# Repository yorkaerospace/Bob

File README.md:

# ARCHIVED REPO
Keeping hardware and software in the same repository causes headache on top of headache. To that end, this repo was archived on 2023-07-08 and further development will continue in the following repos:
- [ProtonNumber/Bob-Firmware](https://github.com/ProtonNumber/Bob-Firmware)  
- [ProtonNumber/Bob-Hardware](https://github.com/ProtonNumber/Bob-Hardware)
- [ProtonNumber/Bob-Drivers](https://github.com/ProtonNumber/Bob-Drivers)

# Bob

Simple RP2040 based datalogger.

## Rev 3 Specs:

 - 8MB of flash storage (Winbond W25Q64)
 - Barometer/Altimiter (HopeRF HP203B)
 - 6-Axis IMU (QST QMI8658C)
 - 3-Axis Magnetometer (QST QMC5883L)
 
 See docs folder for datasheets.

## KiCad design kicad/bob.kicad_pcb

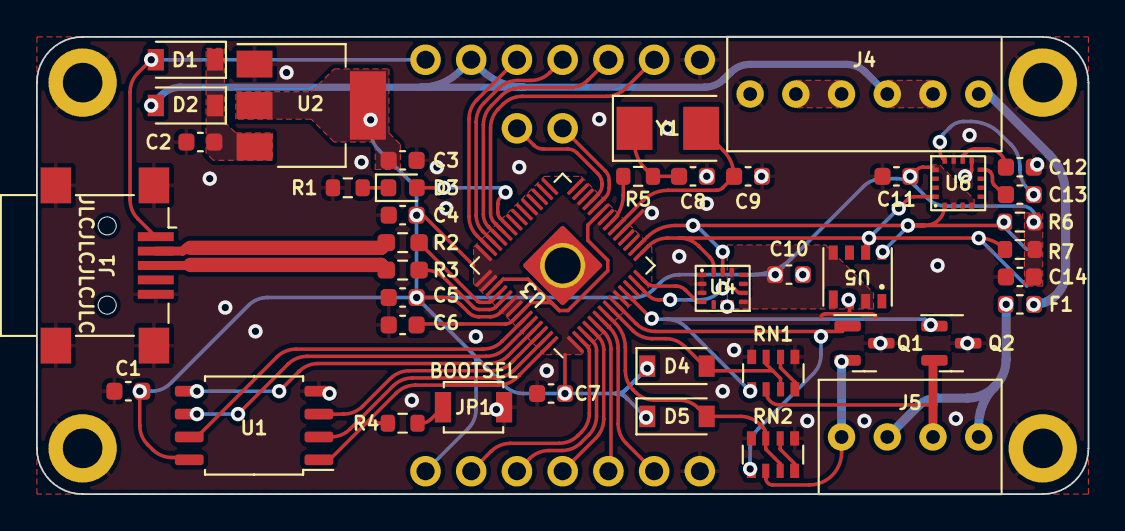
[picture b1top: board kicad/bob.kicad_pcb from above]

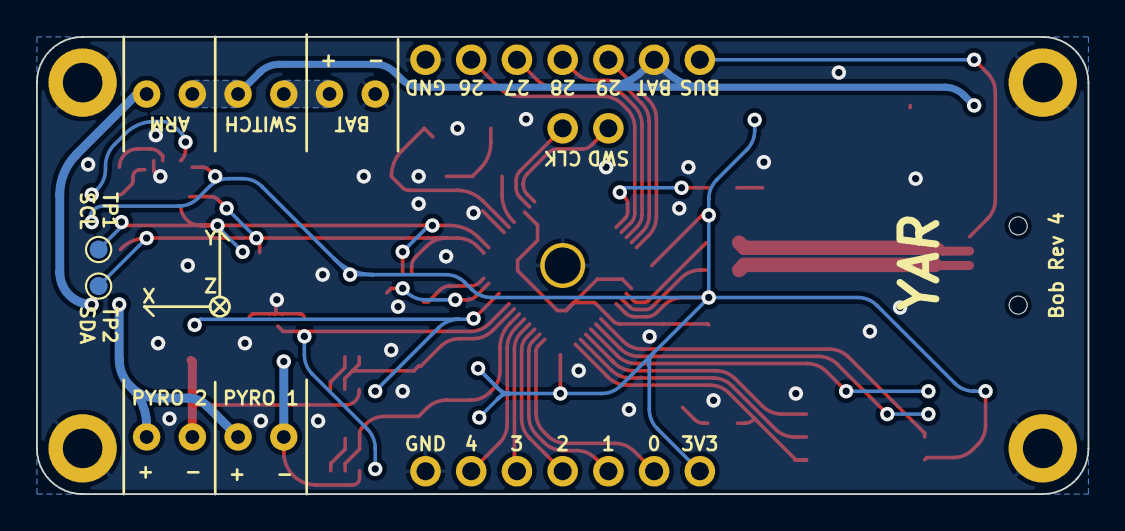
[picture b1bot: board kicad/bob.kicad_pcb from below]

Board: 2 copper layers, 58.4 x 25.4 mm, 52 parts (4 on the bottom side), 51 nets.

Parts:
C1, C5, C7, C10, C11, C14: 100n; C_0603_1608Metric
C2, C3: 10u; C_0603_1608Metric
C4, C6: 1u; C_0603_1608Metric
C8, C9: 4p; C_0603_1608Metric
C12: 4.7u; C_0603_1608Metric
C13: 220n; C_0603_1608Metric
D1, D2, D4, D5: 1N4007; D_SOD-123
D3: RED; LED_0603_1608Metric
F1: Polyfuse; Fuse_0603_1608Metric
H1, H2, H3, H4: MountingHole_Pad; MountingHole_2.2mm_M2_DIN965_Pad
J1: Mini USB Female; USB_Mini-B_Lumberg_2486_01_Horizontal
J2, J3: GPIO (Optional); PinHeader_1x07_P2.54mm_Vertical_NoSilk
J4: Screw Terminal, 2.54mm; ScrewTerm_2.54x06
J5: Conn_01x04_Male; ScrewTerm_2.54x04
J6: Conn_01x03_Male; PinHeader_1x02_P2.54mm_Vertical
JP1: BOOTSEL; SW_SPST_B3U-1000P
Q1, Q2: IRFML8244TRPBF; SOT-23
R1: 220; R_0603_1608Metric
R2, R3: 27; R_0603_1608Metric_Pad0.98x0.95mm_HandSolder
R4, R5: 1k; R_0603_1608Metric
R6, R7: 10k; R_0603_1608Metric
RN1, RN2: 22k; R_Array_Convex_4x0603
TP1, TP2: TestPoint; TestPoint_Pad_D1.0mm
U1: W25Q64JVSS; SOIC-8_5.23x5.23mm_P1.27mm
U2: AMS1117-3.3; SOT-223-3_TabPin2
U3: RP2040; RP2040-QFN-56_HS
U4: QMI8658C; QMI8658C-LGA14
U5: HP203B; HP203B-LGA8
U6: QMC5883L; QMC5883L-LGA16
Y1: 12MHz; Crystal_SMD_5032-2Pin_5.0x3.2mm
YAR: LOGO; YAR_Logo

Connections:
+1V1: C6.1, U3.23 (DVDD), U3.45 (VREG_VOUT), U3.50 (DVDD)
+3V3: C1.1, C3.1, C4.1, C5.1, C7.1, C10.1, C11.1, C14.1, D4.1 (K), D5.1 (K), J3.1, R6.2, R7.2, U1.8 (VCC), U2.2 (VO), U3.1 (IOVDD), U3.10 (IOVDD), U3.22 (IOVDD), U3.26 (RUN), U3.33 (IOVDD), U3.42 (IOVDD), U3.43 (ADC_AVDD), U3.44 (VREG_IN), U3.48 (USB_VDD), U3.49 (IOVDD), U4.8 (VDD), U4.12 (CS), U5.3 (VDD), U5.8 (CSB), U6.2 (VDD), U6.4 (S1), U6.13 (VIO)
+BATT: D2.2 (A), J2.2, J4.4, J4.5
ARM: F1.2, J5.2, J5.4
Cont 1: D5.2 (A), RN2.3 (R3.1), RN2.7 (R2.2), U3.7 (GPIO5)
Cont 2: D4.2 (A), RN1.3 (R3.1), RN1.7 (R2.2), U3.8 (GPIO6)
Fire 1: J5.1, Q1.2 (D), RN2.2 (R2.1)
Fire 2: J5.3, Q2.2 (D), RN1.2 (R2.1)
GND: C1.2, C2.2, C3.2, C4.2, C5.2, C6.2, C7.2, C8.1, C9.1, C10.2, C11.2, C12.1, C14.2, H1.1, H2.1, H3.1, H4.1, J1.5 (GND), J1.6 (Shield), J2.7, J3.7, J4.1, JP1.1 (A), Q1.3 (S), Q2.3 (S), R1.2, RN1.5 (R4.2), RN1.8 (R1.2), RN2.5 (R4.2), RN2.8 (R1.2), U1.4 (GND), U2.1 (GND), U3.19 (TESTEN), U3.57 (GND), U4.1 (SDO/SA0), U4.2 (SDX), U4.3 (SCX), U4.6 (GND), U4.7 (GND), U5.2 (GND), U6.9 (GND), U6.11 (GND)
GPIO0: J3.2, U3.2 (GPIO0)
GPIO1: J3.3, U3.3 (GPIO1)
GPIO2: J3.4, U3.4 (GPIO2)
GPIO3: J3.5, U3.5 (GPIO3)
GPIO4: J3.6, U3.6 (GPIO4)
GPIO26: J2.6, U3.38 (GPIO26_ADC0)
GPIO27: J2.5, U3.39 (GPIO27_ADC1)
GPIO28: J2.4, U3.40 (GPIO28_ADC2)
GPIO29: J2.3, U3.41 (GPIO29_ADC3)
I2C_SCL: R6.1, TP1.1, U3.16 (GPIO13), U4.13 (SCL), U5.5 (SCL), U6.1 (SCL)
I2C_SDA: R7.1, TP2.1, U3.15 (GPIO12), U4.14 (SDA), U5.6 (SDA), U6.16 (SDA)
unnamed: C2.1, D1.1 (K), D2.1 (K), U2.3 (VI)
unnamed: C8.2, R5.1, Y1.1
unnamed: C12.2, U6.10 (C1)
unnamed: C13.1, U6.8 (SETP)
unnamed: C13.2, U6.12 (SETC)
unnamed: D3.1 (K), R1.1
unnamed: D3.2 (A), U3.37 (GPIO25)
unnamed: F1.1, J4.6
unnamed: J4.2, J4.3
unnamed: JP1.2 (B), R4.1
unnamed: R3.1, U3.47 (USB_DP)
unnamed: R2.1, U3.46 (USB_DM)
unnamed: RN2.4 (R4.1), RN2.6 (R3.2)
unnamed: RN1.4 (R4.1), RN1.6 (R3.2)
Pyro 1: Q1.1 (G), RN2.1 (R1.1), U3.9 (GPIO7)
Pyro 2: Q2.1 (G), RN1.1 (R1.1), U3.11 (GPIO8)
QMI_INT1: U3.14 (GPIO11), U4.4 (INT1)
QMI_INT2: U3.13 (GPIO10), U4.9 (INT2)
QSPI_SCLK: U1.6 (CLK), U3.52 (QSPI_SCLK)
QSPI_SD0: U1.5 (DI(IO0)), U3.53 (QSPI_SD0)
QSPI_SD1: U1.2 (DO(IO1)), U3.55 (QSPI_SD1)
QSPI_SD2: U1.3 (IO2), U3.54 (QSPI_SD2)
QSPI_SD3: U1.7 (IO3), U3.51 (QSPI_SD3)
QSPI_SS: R4.2, U1.1 (~CS), U3.56 (QSPI_SS)
SWCLK: J6.2, U3.24 (SWCLK)
SWD: J6.1, U3.25 (SWD)
USB_D+: J1.3 (D+), R3.2
USB_D-: J1.2 (D-), R2.2
VBUS: D1.2 (A), J1.1 (VBUS), J2.1
XIN: C9.2, U3.20 (XIN), Y1.2
XOUT: R5.2, U3.21 (XOUT)

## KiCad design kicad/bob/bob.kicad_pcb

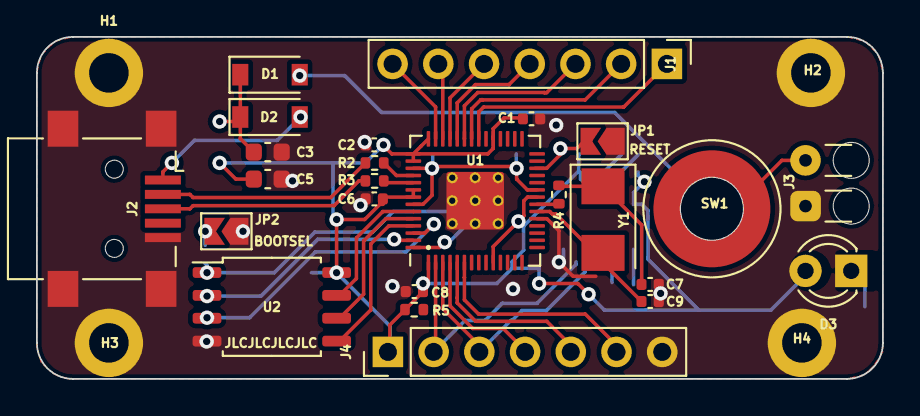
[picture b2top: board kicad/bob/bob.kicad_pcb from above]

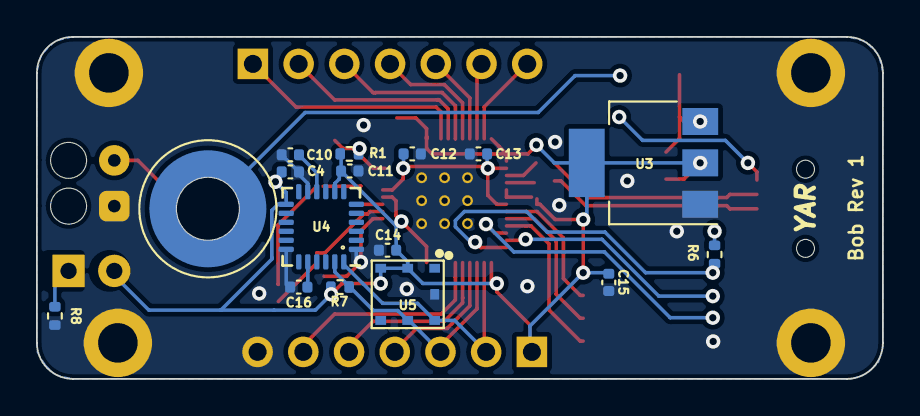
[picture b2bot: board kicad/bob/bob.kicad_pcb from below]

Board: 2 copper layers, 47.0 x 19.0 mm, 45 parts (16 on the bottom side), 37 nets.

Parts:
C1, C4, C6, C8, C10, C11, C12, C14, C15: 100n; C_0402_1005Metric
C2, C13, C16: 1u; C_0402_1005Metric
C3, C5: 10u; C_0603_1608Metric
C7, C9: 27p; C_0402_1005Metric
D1, D2: 1N4007; D_SOD-123
D3: RED; LED_D3.0mm
H1, H2, H3, H4: MountingHole_Pad; MountingHole_2.2mm_M2_DIN965_Pad
J1, J4: GPIO (Optional); PinHeader_1x07_P2.54mm_Vertical
J2: Mini USB Female; USB_Mini-B_Lumberg_2486_01_Horizontal
J3: Battery Connector; Compact_Relief
JP1: RESET; SolderJumper-2_P1.3mm_Open_TrianglePad1.0x1.5mm
JP2: BOOTSEL; SolderJumper-2_P1.3mm_Open_TrianglePad1.0x1.5mm
R1, R4, R6, R8: 1k; R_0402_1005Metric
R2, R3: 27; R_0402_1005Metric
R5, R7: 4k7; R_0402_1005Metric
SW1: Screw Switch; Screw_Switch_M3
U1: RP2040; RP2040-QFN-56
U2: W25Q64JVSS; SOIC-8_5.23x5.23mm_P1.27mm
U3: NCP1117-3.3_SOT223; SOT-223-3_TabPin2
U4: MPU-6050; InvenSense_QFN-24_4x4mm_P0.5mm
U5: BMP180
Y1: 12MHz; Crystal_SMD_5032-2Pin_5.0x3.2mm
YAR: LOGO; YAR_Logo_Small

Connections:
+1V1: C12.1, C13.1, U1.23 (DVDD), U1.45 (VREG_VOUT), U1.50 (DVDD)
+3V3: C1.1, C2.1, C4.1, C5.1, C6.1, C8.1, C11.1, C14.1, C15.1, D3.2 (A), J4.1, R1.1, R5.2, R7.2, U1.1 (IOVDD), U1.10 (IOVDD), U1.22 (IOVDD), U1.33 (IOVDD), U1.42 (IOVDD), U1.43 (ADC_AVDD), U1.44 (VREG_IN), U1.48 (USB_VDD), U1.49 (IOVDD), U2.8 (VCC), U3.2 (VO), U4.8 (VDDIO), U4.13 (VDD), U5.2 (VDD), U5.3 (VDDIO)
+BATT: D1.2 (A), SW1.2
GND: C1.2, C2.2, C3.2, C4.2, C5.2, C6.2, C7.1, C8.2, C9.1, C10.2, C11.2, C12.2, C13.2, C14.2, C15.2, C16.2, H1.1, H2.1, H3.1, H4.1, J2.5 (GND), J2.6 (Shield), J3.1, J4.7, JP1.1 (A), JP2.1 (A), R8.2, U1.19 (TESTEN), U1.57 (GND), U2.4 (GND), U3.1 (GND), U4.1 (CLKIN), U4.9 (AD0), U4.11 (FSYNC), U4.18 (GND), U5.7 (GND)
GPIO2: J4.4, U1.4 (GPIO2)
GPIO3: J4.5, U1.5 (GPIO3)
GPIO4: J4.6, U1.6 (GPIO4)
GPIO23: J1.1, U1.35 (GPIO23)
GPIO24: J1.2, U1.36 (GPIO24)
GPIO25: J1.3, U1.37 (GPIO25)
GPIO26: J1.4, U1.38 (GPIO26_ADC0)
GPIO27: J1.5, U1.39 (GPIO27_ADC1)
GPIO28: J1.6, U1.40 (GPIO28_ADC2)
GPIO29: J1.7, U1.41 (GPIO29_ADC3)
I2C_SCL: J4.3, R7.1, U1.3 (GPIO1), U4.23 (SCL), U5.5 (SCL)
I2C_SDA: J4.2, R5.1, U1.2 (GPIO0), U4.24 (SDA), U5.6 (SDA)
unnamed: C7.2, R4.1, Y1.1
unnamed: C10.1, U4.10 (REGOUT)
unnamed: C16.1, U4.20 (CPOUT)
unnamed: C3.1, D1.1 (K), D2.1 (K), U3.3 (VI)
unnamed: D3.1 (K), R8.1
unnamed: J3.2, SW1.1
unnamed: JP1.2 (B), R1.2, U1.26 (RUN)
unnamed: JP2.2 (B), R6.1
unnamed: R3.1, U1.47 (USB_DP)
unnamed: R2.1, U1.46 (USB_DM)
QSPI_SCLK: U1.52 (QSPI_SCLK), U2.6 (CLK)
QSPI_SD0: U1.53 (QSPI_SD0), U2.5 (DI(IO0))
QSPI_SD1: U1.55 (QSPI_SD1), U2.2 (DO(IO1))
QSPI_SD2: U1.54 (QSPI_SD2), U2.3 (IO2)
QSPI_SD3: U1.51 (QSPI_SD3), U2.7 (IO3)
QSPI_SS: R6.2, U1.56 (QSPI_SS), U2.1 (~CS)
USB_D+: J2.3 (D+), R3.2
USB_D-: J2.2 (D-), R2.2
VBUS: D2.2 (A), J2.1 (VBUS)
XIN: C9.2, U1.20 (XIN), Y1.2
XOUT: R4.2, U1.21 (XOUT)

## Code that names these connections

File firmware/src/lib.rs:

#![no_std]
#![no_main]

use defmt::*;
use defmt_rtt as _;
use panic_probe as _;
use rp2040_hal as hal;

use hal::gpio;

use embedded_hal_compat::{ForwardCompat, ReverseCompat};
use fugit::RateExtU32;
use hp203b::HP203B;
use ouroboros::self_referencing;
use shared_bus::{BusManagerSimple, I2cProxy};

type I2C = hal::I2C<hal::pac::I2C0, (gpio::bank0::Gpio16, gpio::bank0::Gpio17)>;
type I2CHolder<'a> = I2cProxy<'a, I2C>;

// TODO: implement
pub struct Buzzer(gpio::bank0::Gpio5);

// TODO: fix ouroboros?
// TODO:
// - flash
// - IMU
// - magnetometer
#[self_referencing]
pub struct Peripherals {
    _i2c: BusManagerSimple<I2C>,
    #[borrows(_i2c)]
    pub altimeter_thermometer: HP203B<I2CHolder<'this>, hp203b::csb::CSBHigh>,
    pub buzzer: Buzzer,
    pub gpio0: gpio::bank0::Gpio0,
    pub gpio1: gpio::bank0::Gpio1,
    pub gpio2: gpio::bank0::Gpio2,
    pub gpio3: gpio::bank0::Gpio3,
    pub gpio4: gpio::bank0::Gpio4,
    pub gpio26: gpio::bank0::Gpio26,
    pub gpio27: gpio::bank0::Gpio27,
    pub gpio28: gpio::bank0::Gpio28,
    pub gpio29: gpio::bank0::Gpio29,
}

impl Peripherals {
    pub fn take(alti_osr: hp203b::OSR, alti_ch: hp203b::Channel) -> Self {
        info!("Initialising Bob Peripherals");

        let mut perips = hal::pac::Peripherals::take().unwrap();
        let sio = hal::Sio::new(perips.SIO);
        let pins = gpio::Pins::new(
            perips.IO_BANK0,
            perips.PADS_BANK0,
            sio.gpio_bank0,
            &mut perips.RESETS,
        );

        let i2c = BusManagerSimple::new(hal::I2C::new_controller(
            perips.I2C0,
            pins.gpio16.into_mode(),
            pins.gpio17.into_mode(),
            400.kHz(),
            &mut perips.RESETS,
            125_000_000.kHz(),
        ));

        info!("Initialising altimeter...");
        let mut altimeter =
            HP203B::<_, hp203b::csb::CSBHigh>::new(i2c.acquire_i2c().forward(), alti_osr, alti_ch)
                .unwrap();

        Self {
            _i2c: i2c,
            altimeter_thermometer: altimeter,
            buzzer: Buzzer(pins.gpio5),
            gpio0: pins.gpio0,
            gpio1: pins.gpio1,
            gpio2: pins.gpio2,
            gpio3: pins.gpio3,
            gpio4: pins.gpio4,
            gpio26: pins.gpio26,
            gpio27: pins.gpio27,
            gpio28: pins.gpio28,
            gpio29: pins.gpio29,
        }
    }
}

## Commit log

2022-07-04 Initial commit, create gitignore
2022-07-04 Add kicad files
2022-07-04 Removed gbr files, fixed gitignore
2022-07-04 Rearranged directories
2022-07-04 Fixed issues with USB impedance
2022-07-10 Added libraries
2022-07-11 Created a simple BMP driver, and some helper thingys.
2022-07-11 Missed a semicolon
2022-07-15 WIP: started the poller loop
2022-07-21 Added notes from assembling PCB
2022-07-24 Fixed MPU6050 charge pump cap
2022-07-24 Replaced BMP180 with HP203B
2022-07-24 Added piezo buzzer
2022-07-24 Moved I2C to bottom of RP2040
2022-07-24 Changed 0402s to 0603s
2022-07-24 Added SWD connector and test points
2022-07-24 Broke out VBAT
2022-07-25 Added a magnetometer
2022-07-28 Rev 3, issued for production
2022-07-28 Added addresses to I2C bus
2022-07-28 Fixed issues and reissued for production
2022-08-21 Added design notes from REV 3
2022-08-22 Added address for QMC5883L
2022-08-22 Added Kicad Libs. Added thermal relief.
2022-08-22 Added nice symbols to schematic
2022-08-22 Changed LED current limiter so it wont be so bright
2022-08-22 Changed SW1 to a button
2022-08-22 Nope, switch wont fit :(
2022-08-22 Updated footprints to be much saner
2022-08-22 Removed old libs
2022-08-22 Changed U3 to the new symbol libs
2022-08-22 Got rid of old Bob 2 Firmware. It would never work anyways.
2022-08-23 Removed #auto_saved_files#
2022-08-23 Added #auto_saved_files# to gitignore
2022-08-23 Updated Libs
2022-08-23 Started on a HP203B driver
2022-08-30 Fixed endianess of HP203GetTemp/GetPres
2022-08-30 Added CMake stuff
2022-08-30 Made a cursed shell script because i dont like CMake
2022-08-30 Removed tonnes of stuff added by mistake
2022-08-30 Added gitignore
2022-08-30 Piped args to CMake
2022-08-30 Removed BMP180 libs
2022-08-30 Echoed the path that the script plans to remove
2022-09-06 feat: basic rust firmware frame
2022-09-06 Updated documentation
2022-09-06 refactor: turn into a board support crate with a default binary
2022-09-07 Fixed very minor alignment issue that was annoying me.
2022-09-07 Added target_link_libaries
2022-09-07 Fixed some strange CMake issue I dont understand.
2022-09-07 Removed default values from structs, those dont work at all.
2022-09-07 Found the missing semicolon
2022-09-07 Fixed some variable names
2022-09-07 I still dont understand CMAKE. It builds now. Leave me alone.
2022-09-09 Changed OSR and CHN constants over to enums to prevent me-related stupidity.
2022-09-09 Added some documentation to the start of the header
2022-09-09 HP203Measure should now return correct time
2022-09-09 Created a file for bob-related-constants
2022-09-09 Created a simple command interpreter. Awful midnight code, but it works!
2022-09-10 Fixed bitwise stuff
2022-09-10 Updated usbcmd documentation
2022-09-10 Added todos and updated documentation
2022-09-10 Added BOB_STORAGE constant
2022-09-10 Started work on a magnetometer driver
2022-09-11 Added time to build string
2022-09-11 Added support for the QMC's thermometer
2022-09-11 Refactored to provide more useful error reporting
2022-09-11 Marked QMCGetTemp as broken. The reason seems arcane, but its so unimportant that it should be fine.
2022-09-11 QMCGetTemp no longer breaks everything
2022-09-11 Did... something?
2022-09-12 Refactored error output to be a bit saner
2022-09-12 Slight optimisation to error handling code
2022-09-12 Added more formal board support.
2022-09-12 Used $SCRIPT_DIR rather than relative paths. genBin should be more consistent
2022-09-12 Standardised and optimised error reporting
2022-09-12 GenBin only prompts if bin exists
2022-09-12 You dont have to clear bin at all.
2022-09-17 Removed pico SDK and recursive deps
2022-09-17 updated gitignore to exclude cmake
2022-09-18 Made changes while attempting to debug
2022-09-18 Moved sensors into their own libs
2022-09-18 Moved CMakeLists
2022-09-18 Modified genbin to work with new build infastructure
2022-09-18 Reworked Cmake stuff.
2022-09-18 Fixed includes
2022-09-18 Moved Pico_sdk_import
2022-09-18 Passed arguments to CMake again
2022-09-18 Modified gitignore to include pico_sdk_import
2022-09-18 Made include paths less cursed
2022-09-19 Fixed the awful crash bug that drove me insane
2022-09-19 Fixed CMAKE_ARGS
2022-09-19 Stopped pico_sdk_import.cmake from being ignored
2022-09-21 QMIReadBytes now reads the correct number of bytes
2022-09-22 Fixed bug in QMISetOption
2022-09-23 QMITest now provides more useful output
2022-09-23 Updated documentation in header
2022-09-24 Changed temp to signed int
2022-09-24 Negative temps should now be handled correctly
2022-09-24 Magnetometer data is now just put in an array
2022-09-24 Renamed presTemp for consistency
2022-09-24 Fixed syntax errors
2022-09-24 HP203GetPres returns correct value
2022-09-25 Removed stray printf
2022-09-25 Created module to manage and poll sensors as a unit
2022-09-25 Increased I2C baudrate
2022-09-25 Moved sensor handling onto core 1
2022-09-25 Moved includes to .c file
2022-09-25 Added header guards
2022-09-26 Removed usbcmd
2022-09-26 Created a statemachine to manage program flow
2022-09-26 Added methods for processing data
2022-09-26 Renamed HP203GetPresTemp to HP203GetData for consistency
2022-09-26 Adjusted formatting
2022-09-27 Added storfs to libs.
2022-09-28 Split USB command stuff back off to make it easier to expand
2022-09-28 Created a header for ANSI escape codes
2022-09-28 Added storfs's license
2022-09-28 Removed logging
2022-09-28 Gave up on storfs
2022-09-28 Changed to little-fs
2022-09-30 Removed littlefs
2022-10-18 Added SPIFFS
2022-10-18 Moved Core1 into main.c
2022-10-20 Moved away from using FIFO buffers
2022-10-20 merged stateMachine into main
2022-10-20 Fixed debug prompt not closing
2022-10-20 Moved stateDetect to sensors.c for easier testing
2022-10-21 Started work on flash storage
2022-10-31 Tried to get SPIFFs working
2022-10-31 Removed PICO_SPIFFS; it doesn't work ahyugsdjugadhjsgahjsdgashjasdggasdhj
2022-11-04 Flailed around trying to make the fs work
2022-11-04 Yeah there's nothing good here just ignore it
2022-11-05 Created a very shitty shell script to yeet the serial stuff into a file
2022-11-05 Renamed mtx to bufMtx to avoid confusion
2022-11-05 GOT SOMETHING WORKING POGPOGPOG
2022-11-05 ReadData now takes arguments and trims off whitespace
2022-11-05 Temporarily disabled state machine. Will now log data whenever its not plugged in.
2022-11-05 Fixed a weird crash by waiting
2022-11-05 stop leaving CSVs here
2022-11-08 Added pyro channels Added bendy traces Added status LED Removed buzzer
2022-11-11 Added some checks to stop the 2040 from accessing memory that doesn't exist
2022-11-11 Lowered baud rate to fix issues with HP203
2022-11-11 Started work on bob R4
2022-11-22 Added platformIO config file and somewhat cleaned sensor libs
2022-11-28 Cleaned up the repo and removed unnecessary files (mostly CMake)
2022-11-28 Updated gitignores
2022-11-28 Reformatted qmi8658c.h
2022-11-28 Changed some includes from global/system to local, and vice versa
2022-11-28 Removed unnecessary esle in databuf
2022-11-28 Mild refactoring of cmd.c
2022-11-28 Removed genBin
2022-11-28 Fixed overrun
2022-11-28 Corrected memory miscalculation and added the documentation
2023-03-01 Pushing for meeting
2023-03-01 Firmware
2023-03-05 chore: ignore build dir
2023-03-05 refactor: tighten up readData script
2023-03-12 Cherrypicked Laura's readData
2023-03-12 Tear it down and start over
2023-03-12 Implement basic loop and state transitions
2023-03-12 Copy old sensor init code
2023-03-12 Sneaky missing semicolon <_<
2023-03-13 Added data_out state
2023-03-13 Fleshed out states
2023-03-13 Fleshed out sampler
2023-03-13 Fixed some syntax errors caused by careless copying
2023-03-13 Fixed some include issues, and some embarassing syntax errors
2023-03-13 Added clearFlash function. Could maybe inline it?
2023-03-13 Added clear flash and bootselect to commands list
2023-03-13 Fixed more careless copying
2023-03-13 Actually iterate
2023-03-13 Write down what I'm doing
2023-03-14 Added interrupt guards to logSample
2023-03-14 Moved README to root of firmware
2023-03-14 Fixed typo
2023-03-14 Added PrettyPrint to replace the old debug print
2023-03-14 Display flash used in kiB. Avoids horrifying double cast
2023-03-14 Fixed flash not writing. Forgot that writePtr was not a flash address, but a memory address.
2023-03-14 Added the timestamp to samples
2023-03-14 Added StateDiagram.drawio
2023-03-14 Added StateDiagram.drawio.svg
2023-03-14 Added Pretty diagram
2023-03-15 doc: add wizio-pico note to firmware
2023-03-16 Fixed comparison
2023-03-16 Told the CMAKE SDK how much flash we have
2023-03-16 Added interrupt guards to clearFlash
2023-03-17 Increased sample rate
2023-03-17 Split cmdInterpreter intoits own function
2023-03-17 Created SampleAndLog to simplify main slightly
2023-03-17 Fixed typos
2023-03-17 Readded help text
2023-03-17 Replaced stupid ? with an actually useful error message
2023-03-17 Tried to hide cursor. Kinda worked
2023-03-17 Bodge the HP203 into working
2023-03-17 Fix bug in HP203 Error handling
2023-03-17 Change FLASH_SIZE to PICO_FLASH_SIZE_BYTES for consistency
2023-03-17 Create macros for GYRO_RANGE and ACCL_RANGE
2023-03-17 Added functions to convert from raw measurements to actual units.
2023-03-17 DEBUG_PRINT No longer writes data to flash
2023-03-18 Fixed issues found by pio check.
2023-04-03 Servo Motor test code
2023-06-03 Replace one (1) semicolon
2023-06-12 Resolve merge conflicts
2023-06-12 Add tasklist from Phoenix-sw
2023-06-13 Switched to a tasklist
2023-06-13 Add the rest of the sensors
2023-06-16 Oh god everythings on fire but this might be useful. Yheet!
2023-06-17 Writing hat drivers, AAAAAAAAAAAAAAAAAAAAAAAAAAA
2023-06-17 Switched to pico-lora, rather than my own dodgy port
2023-06-18 Late night flailing around which KINDA WORKED!!!!!!!!!
2023-06-20 Switched to minmea for NMEA parsing, changed packet formatting
2023-06-21 Got a simple shell working
2023-06-22 Added values to states for transmitting
2023-06-22 Started work on flash logger to Lissa's spec
2023-06-23 Changed data field in log to a union, seems to have de-gremilined the flash code
2023-06-24 Increased output frequency
2023-06-24 Created simple driver to read and parse bob's output
2023-06-26 Fiddled around with lora settings
2023-06-26 Shell refactor
2023-06-26 Add IMU data. Gyro is useless
2023-06-26 Set lora params
2023-06-27 Filter acceleration, add it to output
2023-06-27 Changed how VID is calculated, should reduce collisions
2023-06-27 Changed the spinner to use ASCII chars
2023-06-27 Manhattan magnitude fixed, thanks Tails!
2023-07-08 Add archive notice
